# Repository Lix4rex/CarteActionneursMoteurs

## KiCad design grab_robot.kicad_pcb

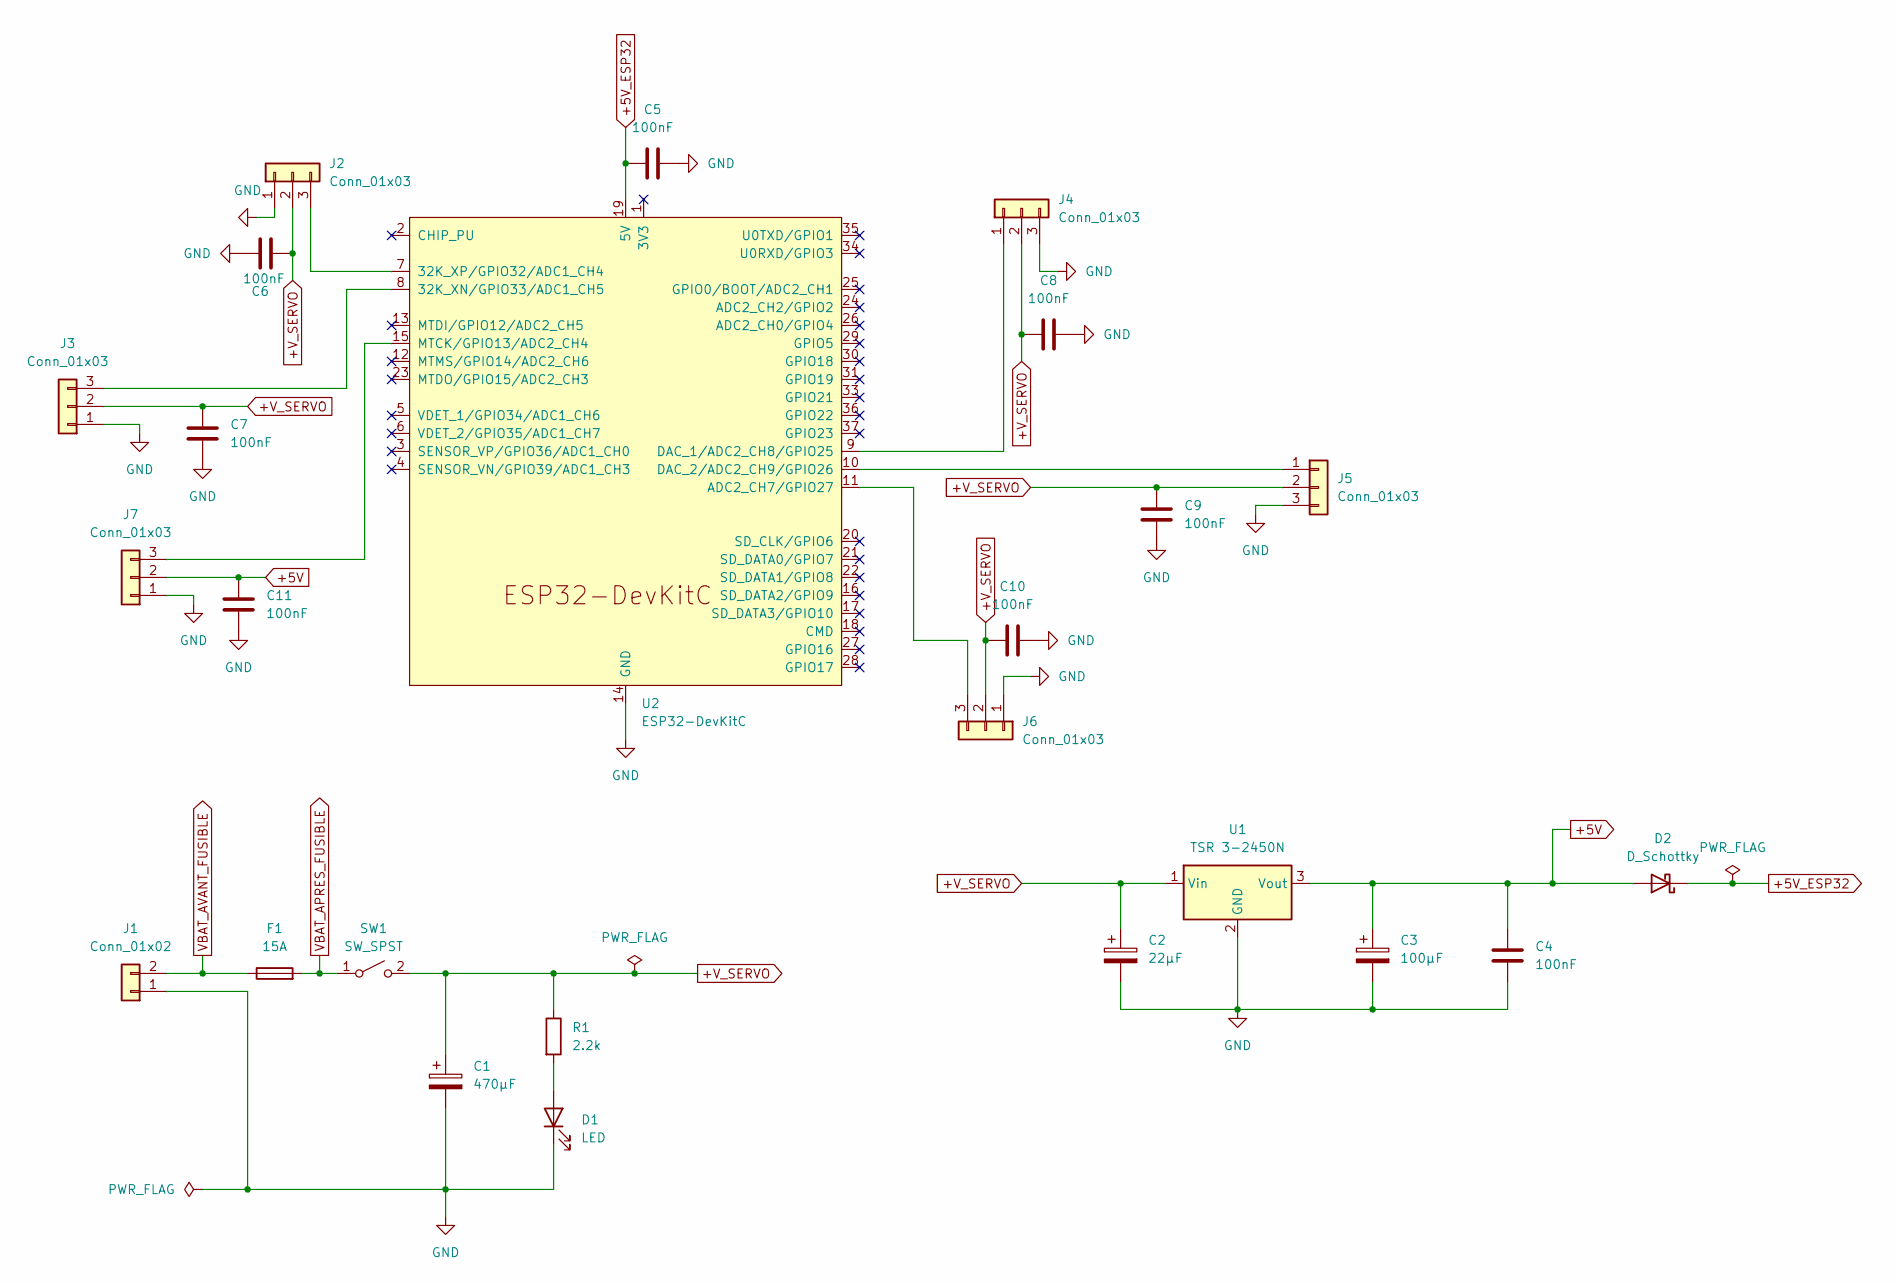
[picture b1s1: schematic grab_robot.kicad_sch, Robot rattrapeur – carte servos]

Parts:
C1: 470µF; CP_Radial_D10.0mm_P5.00mm
C2: 22µF; CP_Radial_D5.0mm_P2.00mm
C3: 100µF; CP_Radial_D6.3mm_P2.50mm
C4, C5, C6, C7, C8, C9, C10, C11: 100nF; C_Disc_D5.0mm_W2.5mm_P5.00mm
D1: LED; LED_D3.0mm
D2: D_Schottky; D_DO-41_SOD81_P10.16mm_Horizontal
F1: 15A; FuseHolder_Blade_ATO_Littelfuse_FLR_178.6165
J1: Conn_01x02; AMASS_XT60PW-M_1x02_P7.20mm_Horizontal
J2, J3, J4, J5, J6, J7: Conn_01x03; PinHeader_1x03_P2.54mm_Vertical
R1: 2.2k; R_Axial_DIN0207_L6.3mm_D2.5mm_P10.16mm_Horizontal
SW1: SW_SPST; TerminalBlock_Phoenix_MKDS-1,5-2-5.08_1x02_P5.08mm_Horizont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
U1: TSR 3-2450N; Converter_DCDC_TRACO_TSR2-24xxN_TSR2-24xxxN_THT
U2: ESP32-DevKitC

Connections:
+5V: C3.1, C4.2, C11.2, D2.2 (A), J7.2, U1.3 (Vout)
+5V_ESP32: C5.1, D2.1 (K), U2.19 (5V)
+V_SERVO: C1.1, C2.1, C6.1, C7.2, C8.2, C9.2, C10.2, J2.2, J3.2, J4.2, J5.2, J6.2, R1.1, SW1.2 (B), U1.1 (Vin)
GND: C1.2, C2.2, C3.2, C4.1, C5.2, C6.2, C7.1, C8.1, C9.1, C10.1, C11.1, D1.1 (K), J1.1, J2.1, J3.1, J4.3, J5.3, J6.1, J7.1, U1.2 (GND), U2.14 (GND), U2.32 (GND), U2.38 (GND)
unnamed: D1.2 (A), R1.2
unnamed: J2.3, U2.7 (32K_XP/GPIO32/ADC1_CH4)
unnamed: J3.3, U2.8 (32K_XN/GPIO33/ADC1_CH5)
unnamed: J4.1, U2.9 (DAC_1/ADC2_CH8/GPIO25)
unnamed: J5.1, U2.10 (DAC_2/ADC2_CH9/GPIO26)
unnamed: J6.3, U2.11 (ADC2_CH7/GPIO27)
unnamed: J7.3, U2.15 (MTCK/GPIO13/ADC2_CH4)
VBAT_APRES_FUSIBLE: F1.2, SW1.1 (A)
VBAT_AVANT_FUSIBLE: F1.1, J1.2

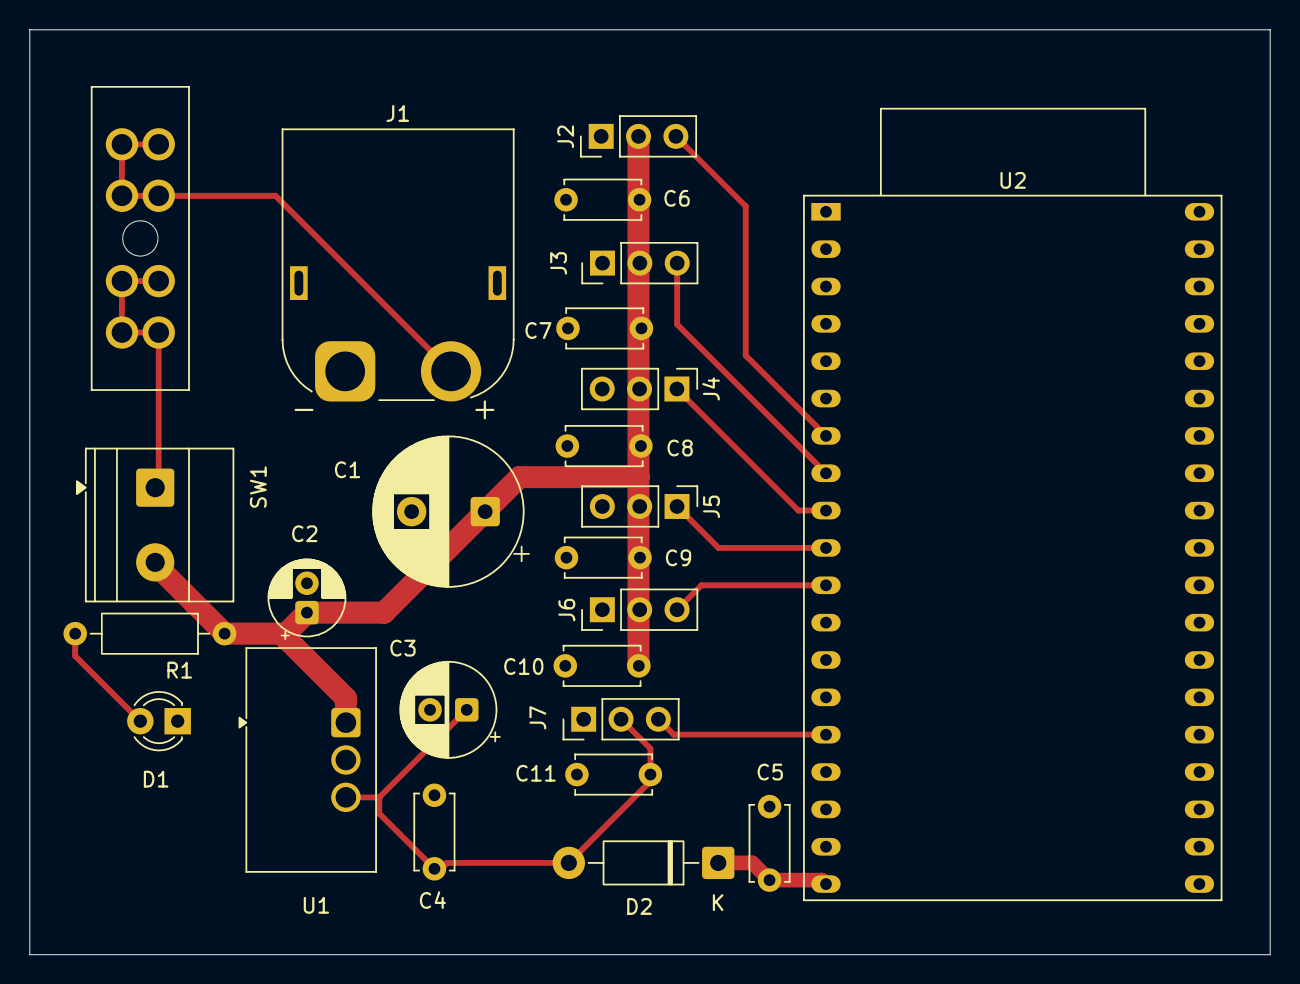
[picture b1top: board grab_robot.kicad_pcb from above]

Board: 2 copper layers, 84.4 x 62.9 mm, 25 parts (0 on the bottom side), 13 nets.
